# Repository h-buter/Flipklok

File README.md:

# Flipklok in 1970s Style with DCF77 Time Synchronization

|  |  |
|----------------------------|-----------------------------|
|                        |                        |

Welcome to the repository for my project as part of my Bachelor's degree in Electronics at Windesheim. This
project involves creating a flip clock inspired by the design from the 1970s, which is synchronized using time
information from the DCF77 long-wave time signal. The goal is to ensure that this electronic and electromechanical
device operates efficiently within a low power environment.

At time of writing I am still deciding on if the clock will be used a desk clock or if I build it in to my 1977 Relaint Robin MK1
This is why some design decisions, like low power, are not always directly clear in the scope of a normal clock project.

For the complete documentation see the doxygen documentation hosted on GitHub pages:
- Index: https://h-buter.github.io/Flipklok/index.html
- Start of code: https://h-buter.github.io/Flipklok/main_8c.html 
- Interactive Bill of materials: https://h-buter.github.io/Flipklok/md_extra-docs_2bom.html

## Project Overview

This flip clock project integrates both mechanical components and electronics to display the current time
accurately based on data received from the DCF77 transmitter located in Germany. Designed with energy efficiency
in mind, the clock maintains continuous time tracking to compensate for any potential reception limitations of the
DCF77 signal while minimizing power consumption.

## Key Challenges

- **Mechanical and Time Management**: The project requires careful application of mechanics and efficient time
management techniques to ensure the device functions optimally on a 12V source.

- **Integration of Electronics and Electromechanics**: Incorporating electronic components like motors and sensors
for position detection into the mechanical design poses significant challenges.

- **PCB Design**: The creation of a custom PCB is necessary to accommodate all electronic components while
maintaining compactness and efficiency.

- **DCF77 Protocol Implementation**: Applying the DCF77 protocol ensures accurate time synchronization. This
involves handling signals and data correctly within the system’s constraints.

- **Software Development**: The software component, developed in C with some sections written in assembly
language, is responsible for processing DCF77 data and controlling stepper or servo motors to operate the flip
clock.

## Project Boundaries

### Software
The software aspect focuses on:
- Processing DCF77 signal data.
- Controlling a stepper/servo motor mechanism to display time changes accurately.

### Hardware
The hardware component involves:
- Integrating electronic and electromechanical components for seamless operation of the flip clock module.
- Receiving and processing DCF77 timing information effectively.

## Getting Started

To get started with this project, you need to:

- Code: 
    - If you want to view the code use the doxygen documentation (see intoduction) or view the source files on GitHub.
    - If you want to run the code, install TI code composer studio and clone this repository.
        - This repo should contain every file to be able to compile the code for the MSP430G2553
- PCB:
    - View the PCB files use the exported pdf: [exported pdf's](https://github.com/h-buter/Flipklok/tree/main/PCB/Flipklok/export)
    - Edit the PCB files, Kicad and clone the repo.
    - Run a production:
        - Download the gerber ZIP and give this to you're favorite PCB manufacturer, it may be possible the etch the board you're self but be warned this is not easy because of the multilayer construction.
        - Order the bom
        - Wait for everything to arrive 
        - Assemble
        - Test, don't let the make smoke out (not optional)
            - First power up test
            - Flash the code, i used a launchpad devboard see page 8 till 10 [link to datasheet of launchpad](https://www.ti.com/lit/ug/slau772a/slau772a.pdf?ts=1743585388312&ref_url=https%253A%252F%252Fwww.ti.com%252Ftool%252FMSP-EXP430G2ET%253FkeyMatch%253Dmsp-exp430g2et%2526tisearch%253Duniversal_search)
- Mechanics:
    - To view the 3d files you can use the free viewing program [Edrawings](https://www.edrawingsviewer.com/download-edrawings)
    - To edit the files you will need Solidworks

## Contribution

Contributions are welcome! Whether it's optimizing the code for better performance or suggesting improvements in
hardware integration, your input is valuable.

## License

This project is licensed under to be determined 

---

Thank you for exploring this unique blend of vintage design and electronics. Should you have any questions
or suggestions regarding this project, feel free to open an issue or contact me directly.

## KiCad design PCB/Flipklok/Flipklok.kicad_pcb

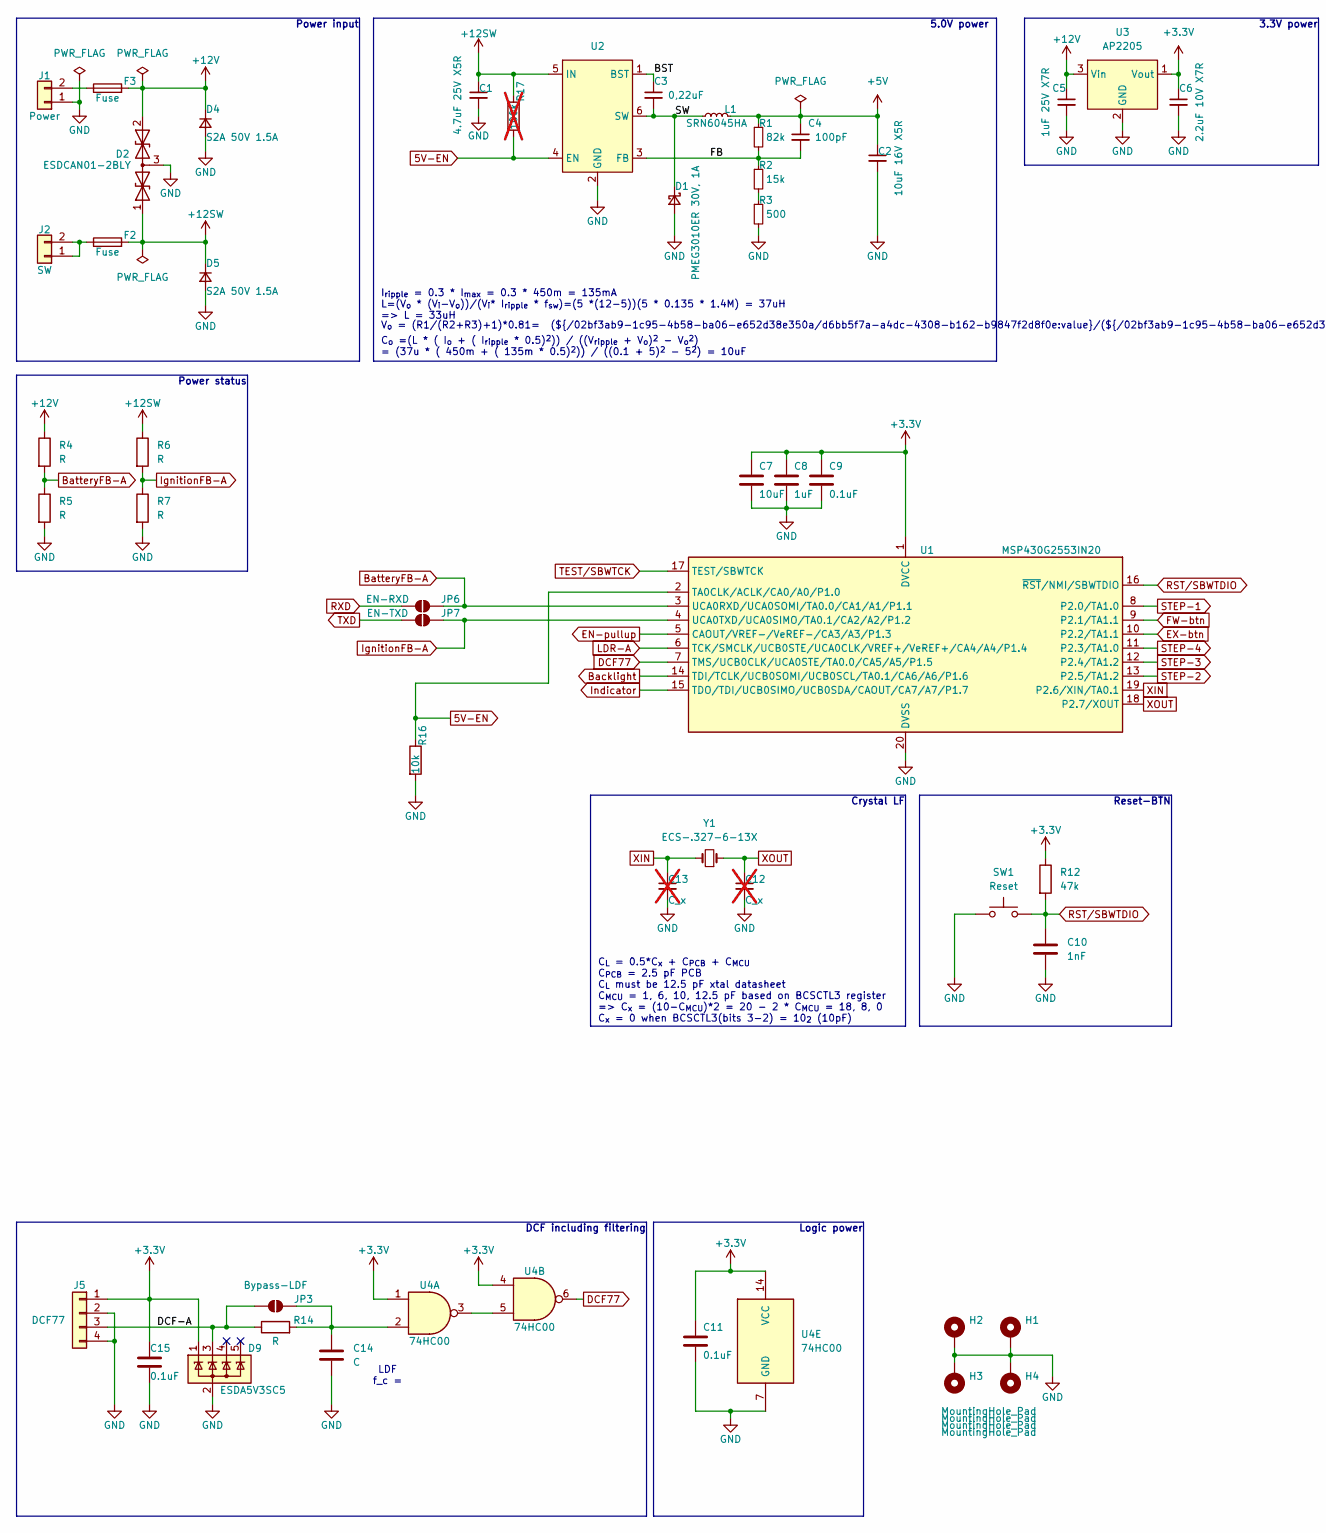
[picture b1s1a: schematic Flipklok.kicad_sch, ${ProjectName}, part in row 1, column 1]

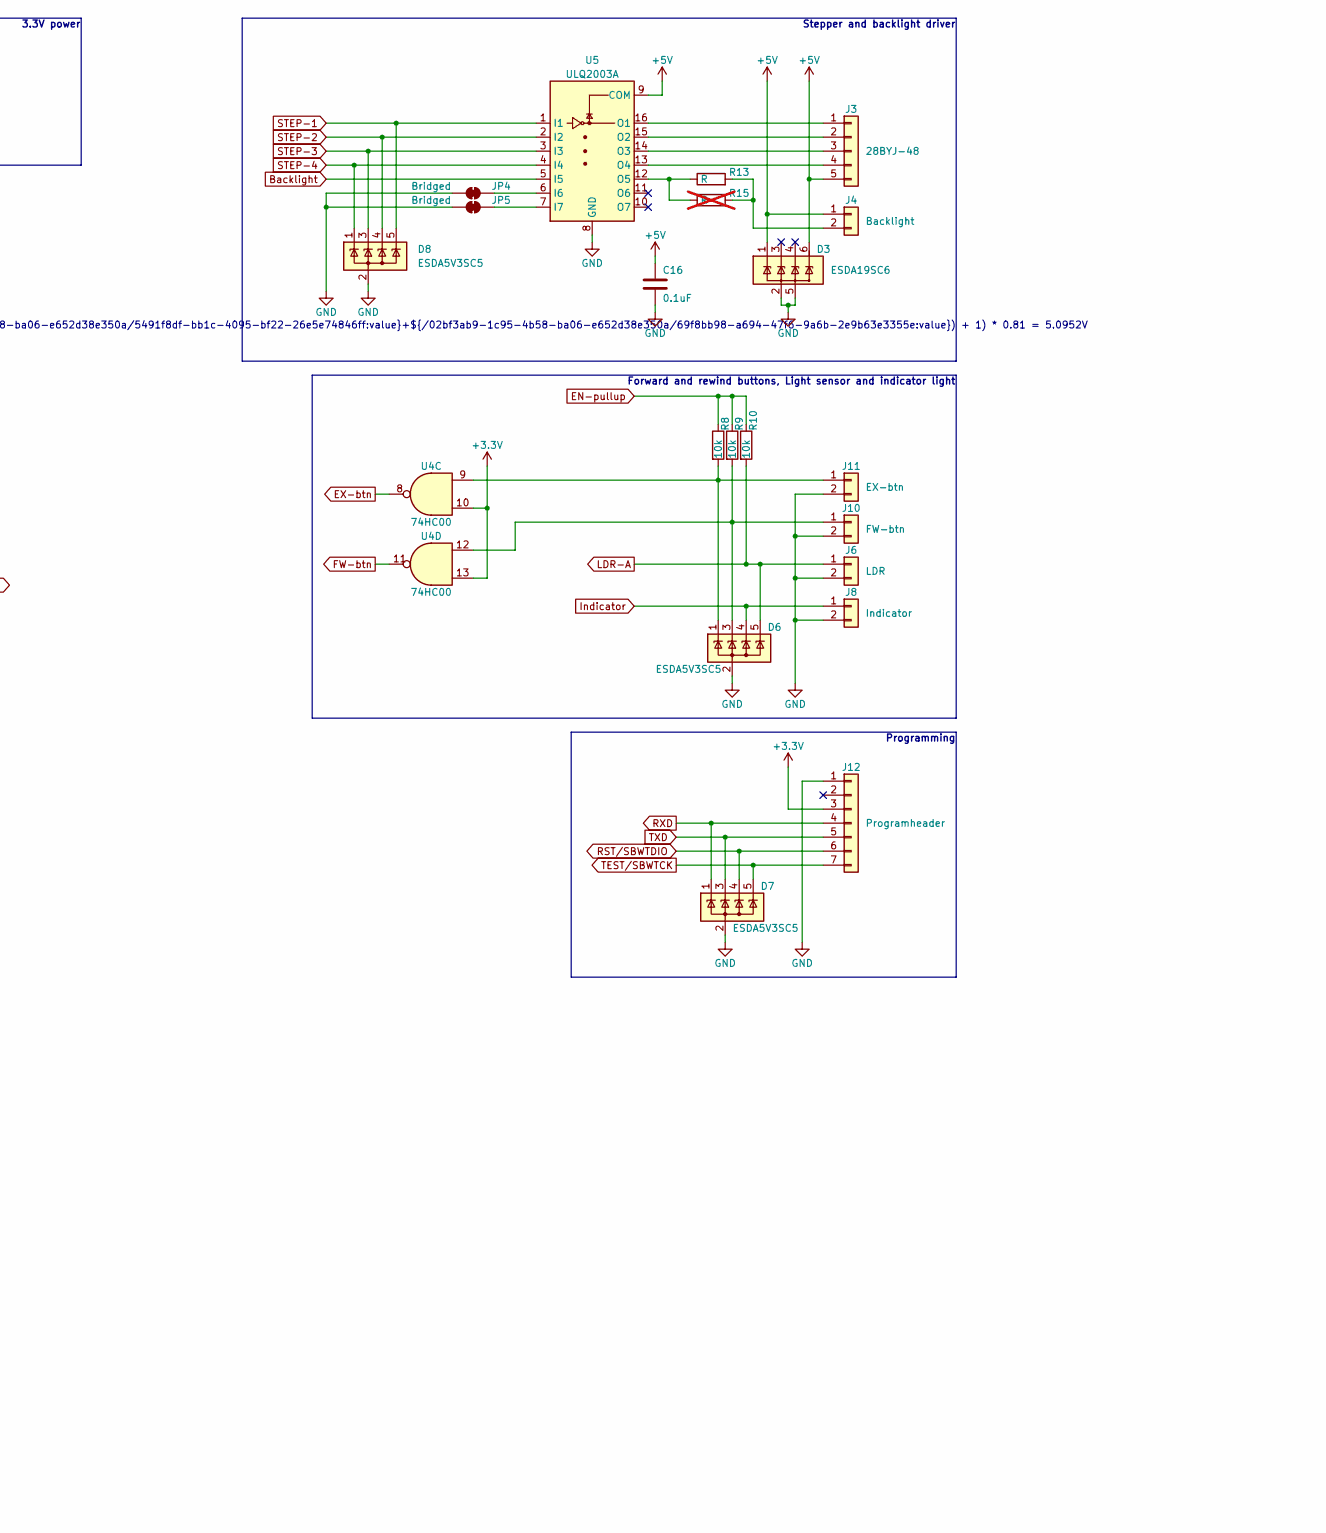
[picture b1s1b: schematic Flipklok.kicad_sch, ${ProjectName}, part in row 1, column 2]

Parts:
C1: 4.7uF 25V X5R; C_0805_2012Metric_Pad1.18x1.45mm_HandSolder
C2: 10uF 16V X5R; C_0805_2012Metric_Pad1.18x1.45mm_HandSolder
C3: 0,22uF; C_0805_2012Metric_Pad1.18x1.45mm_HandSolder
C4: 100pF; C_0805_2012Metric_Pad1.18x1.45mm_HandSolder
C5: 1uF 25V X7R; C_0805_2012Metric_Pad1.18x1.45mm_HandSolder
C6: 2.2uF 10V X7R; C_0805_2012Metric_Pad1.18x1.45mm_HandSolder
C7: 10uF; C_0805_2012Metric_Pad1.18x1.45mm_HandSolder
C8: 1uF; C_0805_2012Metric_Pad1.18x1.45mm_HandSolder
C9, C11, C15, C16: 0.1uF; C_0805_2012Metric_Pad1.18x1.45mm_HandSolder
C10: 1nF; C_0805_2012Metric_Pad1.18x1.45mm_HandSolder
C12, C13: C_x; C_0805_2012Metric_Pad1.18x1.45mm_HandSolder; not fitted
C14: C; C_0805_2012Metric_Pad1.18x1.45mm_HandSolder
D1: PMEG3010ER 30V, 1A; D_SOD-123F
D2: ESDCAN01-2BLY; TSOT-23
D3: ESDA19SC6; SOT-23-6_Handsoldering
D4, D5: S2A 50V 1.5A; D_SMB_Handsoldering
D6, D7, D8, D9: ESDA5V3SC5; SOT-23-5
F2, F3: Fuse; Fuse_0603_1608Metric_Pad1.05x0.95mm_HandSolder
H1, H2, H3, H4: MountingHole_Pad; MountingHole_3.2mm_M3_DIN965_Pad_TopBottom
J1: Power; JST_XH_B2B-XH-A_1x02_P2.50mm_Vertical
J2: SW; JST_XH_B2B-XH-A_1x02_P2.50mm_Vertical
J3: 28BYJ-48; JST_XH_B5B-XH-A_1x05_P2.50mm_Vertical
J4: Backlight; JST_XH_B2B-XH-A_1x02_P2.50mm_Vertical
J5: DCF77; JST_XH_B4B-XH-A_1x04_P2.50mm_Vertical
J6: LDR; JST_XH_B2B-XH-A_1x02_P2.50mm_Vertical
J8: Indicator; JST_XH_B2B-XH-A_1x02_P2.50mm_Vertical
J10: FW-btn; JST_XH_B2B-XH-A_1x02_P2.50mm_Vertical
J11: EX-btn; JST_XH_B2B-XH-A_1x02_P2.50mm_Vertical
J12: Programheader; JST_XH_B7B-XH-A_1x07_P2.50mm_Vertical
JP3: Bypass-LDF; SolderJumper-2_P1.3mm_Open_Pad1.0x1.5mm
JP4, JP5: Bridged; SolderJumper-2_P1.3mm_Bridged_Pad1.0x1.5mm
JP6: EN-RXD; SolderJumper-2_P1.3mm_Open_Pad1.0x1.5mm
JP7: EN-TXD; SolderJumper-2_P1.3mm_Open_Pad1.0x1.5mm
L1: SRN6045HA; L_Bourns_SRN6045TA
R1: 82k; R_0805_2012Metric_Pad1.20x1.40mm_HandSolder
R2: 15k; R_0805_2012Metric_Pad1.20x1.40mm_HandSolder
R3: 500; R_0805_2012Metric_Pad1.20x1.40mm_HandSolder
R4, R5, R6, R7, R13, R14: R; R_0805_2012Metric_Pad1.20x1.40mm_HandSolder
R8, R9, R10, R16: 10k; R_0805_2012Metric_Pad1.20x1.40mm_HandSolder
R12: 47k; R_0805_2012Metric_Pad1.20x1.40mm_HandSolder
R15: R; R_0805_2012Metric_Pad1.20x1.40mm_HandSolder; not fitted
R17: 100k; R_0805_2012Metric_Pad1.20x1.40mm_HandSolder; not fitted
SW1: Reset; SW_Tactile_SPST_NO_Straight_CK_PTS636Sx25SMTRLFS
U1: MSP430G2553IN20; DIP-20_W7.62mm
U2: SOT-23-6_Handsoldering
U3: AP2205; SOT-89-3_Handsoldering
U4: 74HC00; SOIC-14_3.9x8.7mm_P1.27mm
U5: ULQ2003A; DIP-16_W7.62mm_Socket_LongPads
Y1: ECS-.327-6-13X; Crystal_C26-LF_D2.1mm_L6.5mm_Horizontal

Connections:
5V-EN: R16.1, R17.2, U1.2 (TA0CLK/ACLK/CA0/A0/P1.0), U2.4 (EN)
+3.3V: C6.1, C7.1, C8.1, C9.1, C11.1, C15.1, D9.1 (K), J5.1, J12.3, R12.1, U1.1 (DVCC), U3.1 (Vout), U4.1, U4.4, U4.10, U4.13, U4.14 (VCC)
+5V: C2.1, C4.1, C16.1, D3.1 (IO1), D3.6 (IO5), J3.5, J4.1, L1.2, R1.1, U5.9 (COM)
+12SW: C1.1, D2.1 (A1), D5.1 (K), F2.2, R6.1, R17.1, U2.5 (IN)
+12V: C5.1, D2.2 (A2), D4.1 (K), F3.2, R4.1, U3.3 (Vin)
/BST: C3.1, U2.1 (BST)
/DCF-A: D9.3 (K), J5.3, JP3.1 (A), R14.1
/FB: C4.2, R1.2, R2.1, U2.3 (FB)
/SW: C3.2, D1.1 (K), L1.1, U2.6 (SW)
Backlight: U1.14 (TDI/TCLK/UCB0SOMI/UCB0SCL/TA0.1/CA6/A6/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), U5.5 (I5)
BatteryFB-A: JP6.2 (B), R4.2, R5.1, U1.3 (UCA0RXD/UCA0SOMI/TA0.0/CA1/A1/P1.1)
DCF77: U1.7 (TMS/UCB0CLK/UCA0STE/TA0.0/CA5/A5/P1.5), U4.6
EN-pullup: R8.1, R9.1, R10.1, U1.5 (CAOUT/VREF-/VeREF-/CA3/A3/P1.3)
EX-btn: U1.10 (P2.2/TA1.1), U4.8
FW-btn: U1.9 (P2.1/TA1.1), U4.11
GND: C1.2, C2.2, C5.2, C6.2, C7.2, C8.2, C9.2, C10.2, C11.2, C12.2, C13.2, C14.2, C15.2, C16.2, D1.2 (A), D2.3 (common), D3.2 (GND), D3.5 (IO4), D4.2 (A), D5.2 (A), D6.2 (A), D7.2 (A), D8.2 (A), D9.2 (A), H1.1, H2.1, H3.1, H4.1, J1.1, J5.2, J5.4, J6.2, J8.2, J10.2, J11.2, J12.1, JP4.1 (A), JP5.1 (A), R3.2, R5.2, R7.2, R16.2, SW1.1, U1.20 (DVSS), U2.2 (GND), U3.2 (GND), U4.7 (GND), U5.8 (GND)
IgnitionFB-A: JP7.2 (B), R6.2, R7.1, U1.4 (UCA0TXD/UCA0SIMO/TA0.1/CA2/A2/P1.2)
Indicator: D6.4 (K), J8.1, U1.15 (TDO/TDI/UCB0SIMO/UCB0SDA/CAOUT/CA7/A7/P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)
LDR-A: D6.5 (K), J6.1, R10.2, U1.6 (TCK/SMCLK/UCB0STE/UCA0CLK/VREF+/VeREF+/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)
unnamed: F3.1, J1.2
unnamed: F2.1, J2.1, J2.2
unnamed: J3.1, U5.16 (O1)
unnamed: J3.2, U5.15 (O2)
unnamed: J3.3, U5.14 (O3)
unnamed: J3.4, U5.13 (O4)
unnamed: J4.2, R13.2, R15.2
unnamed: D6.3 (K), J10.1, R9.2, U4.12
unnamed: D6.1 (K), J11.1, R8.2, U4.9
unnamed: C14.1, JP3.2 (B), R14.2, U4.2
unnamed: JP4.2 (B), U5.6 (I6)
unnamed: JP5.2 (B), U5.7 (I7)
unnamed: R2.2, R3.1
unnamed: U4.3, U4.5
unnamed: R13.1, R15.1, U5.12 (O5)
RST/SBWTDIO: C10.1, D7.4 (K), J12.6, R12.2, SW1.2, U1.16 (~RST/NMI/SBWTDIO)
RXD: D7.1 (K), J12.4, JP6.1 (A)
STEP-1: D8.5 (K), U1.8 (P2.0/TA1.0), U5.1 (I1)
STEP-2: D8.4 (K), U1.13 (P2.5/TA1.2), U5.2 (I2)
STEP-3: D8.3 (K), U1.12 (P2.4/TA1.2), U5.3 (I3)
STEP-4: D8.1 (K), U1.11 (P2.3/TA1.0), U5.4 (I4)
TEST/SBWTCK: D7.5 (K), J12.7, U1.17 (TEST/SBWTCK)
TXD: D7.3 (K), J12.5, JP7.1 (A)
XIN: C13.1, U1.19 (P2.6/XIN/TA0.1), Y1.2
XOUT: C12.1, U1.18 (P2.7/XOUT), Y1.1

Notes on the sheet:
Power status
I_{ripple} = 0.3 * I_{max} = 0.3 * 450m = 135mA L=(V_{o} * (V_{i}-V_{o}))/(V_{i}* I_{ripple} * f_{sw})=(5 *(12-5))(5 * 0.135 * 1.4M) = 37uH => L = 33uH
LDF f_c =
Power input
Reset-BTN
C_{o} =(L * ( I_{o} + ( I_{ripple} * 0.5)^{2})) / ((V_{ripple} + V_{o})^{2} - V_{o}^{2}) = (37u * ( 450m + ( 135m * 0.5)^{2})) / ((0.1 + 5)^{2} - 5^{2}) = 10uF
5.0V power
Crystal LF
C_{L} = 0.5*C_{x} + C_{PCB} + C_{MCU} C_{PCB} = 2.5 pF PCB C_{L} must be 12.5 pF xtal datasheet C_{MCU} = 1, 6, 10, 12.5 pF based on BCSCTL3 register => C_{x} = (10-C_{MCU})*2 = 20 - 2 * C_{MCU} = 18, 8, 0 C_{x} = 0 when BCSCTL3(bits 3-2) = 10_{2} (10pF)
3.3V power
V_{o} = (R1/(R2+R3)+1)*0.81= (${/02bf3ab9-1c95-4b58-ba06-e652d38e350a/d6bb5f7a-a4dc-4308-b162-b9847f2d8f0e:value}/(${/02bf3ab9-1c95-4b58-ba06-e652d38e350a/5491f8df-bb1c-4095-bf22-26e5e74846ff:value}+${/02bf3ab9-1c95-4b58-ba06-e652d38e350a/69f8bb98-a694-47f6-9a6b-2e9b63e3355e:value}) + 1) * 0.81 = 5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
Forward and rewind buttons, Light sensor and indicator light
DCF including filtering
Programming
Stepper and backlight driver
Logic power

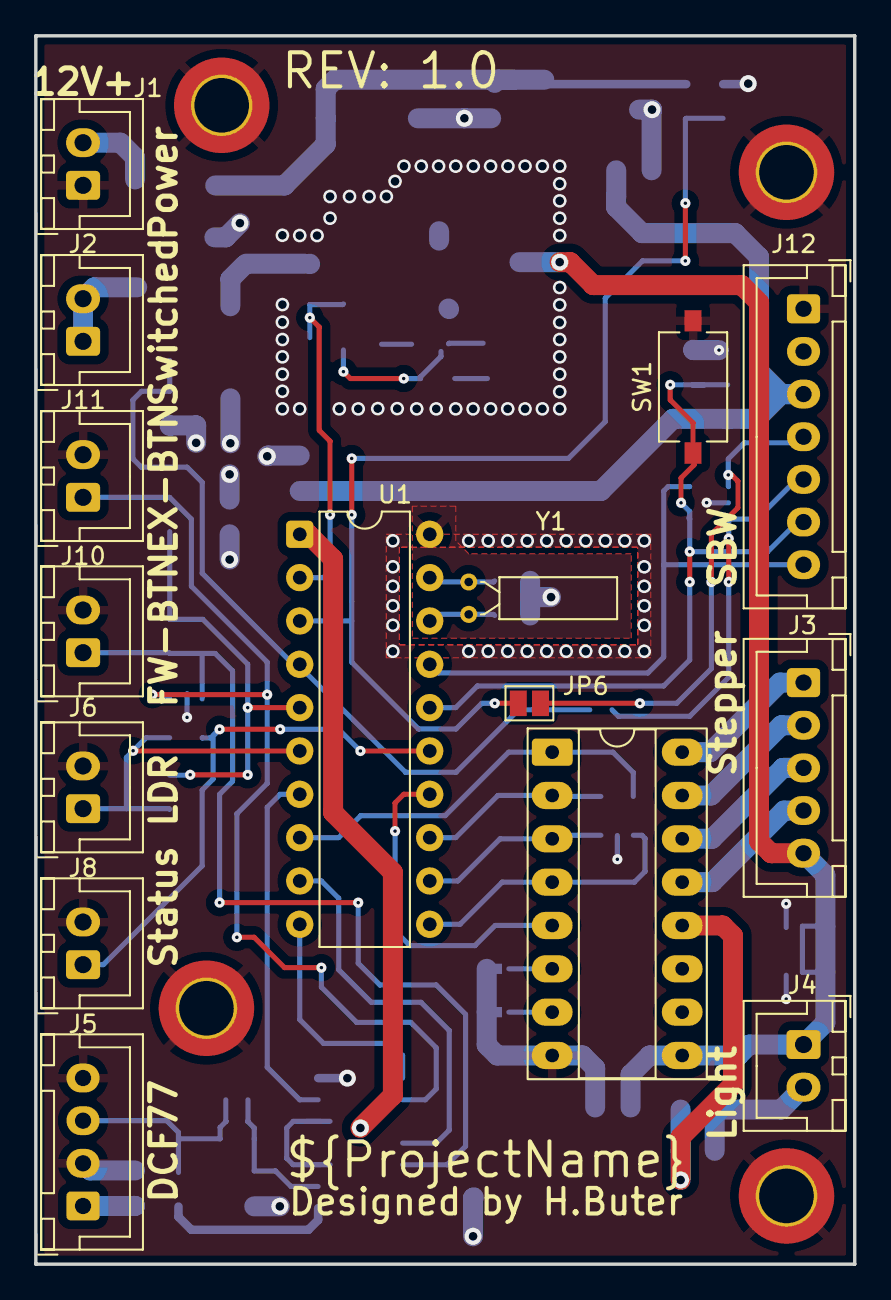
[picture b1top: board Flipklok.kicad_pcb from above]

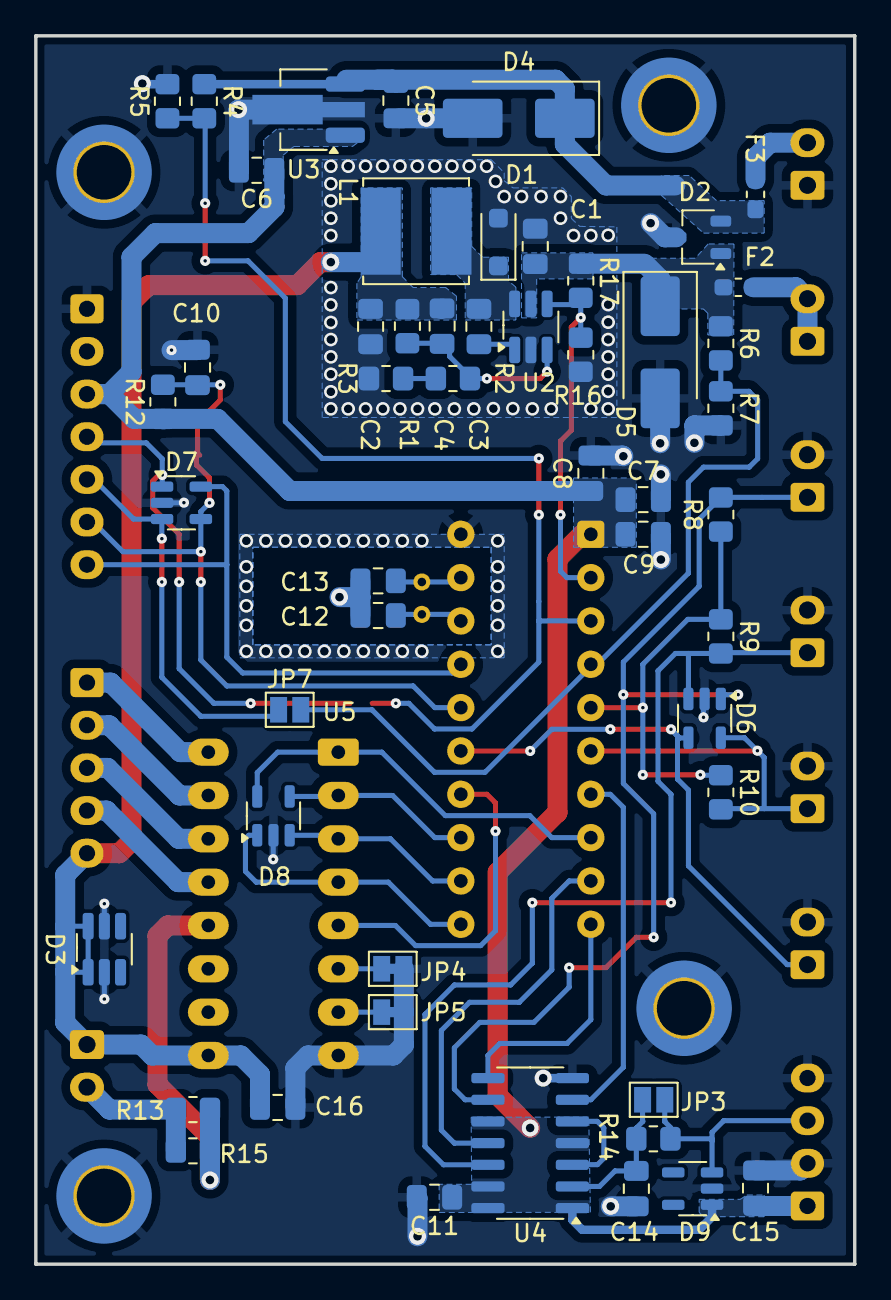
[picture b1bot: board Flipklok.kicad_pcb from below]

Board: 2 copper layers, 48.0 x 72.0 mm, 70 parts (51 on the bottom side), 44 nets.

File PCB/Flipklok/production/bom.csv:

Designator,Footprint,Quantity,Value,LCSC Part #
C1,0805,1,4.7uF 25V X5R,
C10,0805,1,1nF,
"C11, C15, C16, C9",0805,4,0.1uF,
C14,0805,1,C,
C2,0805,1,10uF 16V X5R,
C3,0805,1,"0,22uF",
C4,0805,1,100pF,
C5,0805,1,1uF 25V X7R,
C6,0805,1,2.2uF 10V X7R,
C7,0805,1,10uF,
C8,0805,1,1uF,
D1,D_SOD-123F,1,"PMEG3010ER 30V, 1A",
D2,TSOT-23,1,ESDCAN01-2BLY,
D3,SOT-23-6_Handsoldering,1,ESDA19SC6,
"D4, D5",D_SMB_Handsoldering,2,S2A 50V 1.5A,
"D6, D7, D8, D9",SOT-23-5,4,ESDA5V3SC5,
"F2, F3",0603,2,Fuse,
J1,JST_XH_B2B-XH-A_1x02_P2.50mm_Vertical,1,Power,
J10,JST_XH_B2B-XH-A_1x02_P2.50mm_Vertical,1,FW-btn,
J11,JST_XH_B2B-XH-A_1x02_P2.50mm_Vertical,1,EX-btn,
J12,JST_XH_B7B-XH-A_1x07_P2.50mm_Vertical,1,Programheader,
J2,JST_XH_B2B-XH-A_1x02_P2.50mm_Vertical,1,SW,
J3,JST_XH_B5B-XH-A_1x05_P2.50mm_Vertical,1,28BYJ-48,
J4,JST_XH_B2B-XH-A_1x02_P2.50mm_Vertical,1,Backlight,
J5,JST_XH_B4B-XH-A_1x04_P2.50mm_Vertical,1,DCF77,
J6,JST_XH_B2B-XH-A_1x02_P2.50mm_Vertical,1,LDR,
J8,JST_XH_B2B-XH-A_1x02_P2.50mm_Vertical,1,Indicator,
L1,L_Bourns_SRN6045TA,1,SRN6045HA,
R1,0805,1,82k,
"R10, R16, R8, R9",0805,4,10k,
R12,0805,1,47k,
"R13, R14, R4, R5, R6, R7",0805,6,R,
R2,0805,1,15k,
R3,0805,1,500,
RESET,SW_Tactile_SPST_NO_Straight_CK_PTS636Sx25SMTRLFS,1,Reset,
U1,DIP-20_W7.62mm,1,MSP430G2553IN20,
U2,SOT-23-6_Handsoldering,1,~,
U3,SOT-89-3_Handsoldering,1,AP2205,
U4,SOIC-14_3.9x8.7mm_P1.27mm,1,74HC00,
U5,DIP-16_W7.62mm_Socket_LongPads,1,ULQ2003A,
Y1,Crystal_C26-LF_D2.1mm_L6.5mm_Horizontal,1,ECS-.327-6-13X,

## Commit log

2025-03-03 Update Readme
    added basic project info
2025-03-06 started working on dcf receive test
2025-03-10 Finished basic DCF and NTP check to test DCF77 module reliability
2025-03-10 Started working on mechanics mounting the stepper motor
2025-03-10 Added influxDB support to log errors
2025-03-10 Started working on motor holder v2
2025-03-11 Initial schematic commit Started working on schematic
2025-03-11 Revert "Initial schematic commit Started working on schematic"
    This reverts commit 41658e12fd88ed23b74b87337d35702dc5f5711a.
2025-03-12 Finished REV1.0 of schematic, started working on PCB
2025-03-13 Started optimizing routing and layout
2025-03-14 Finished lay-out and exported gerbers
2025-03-14 Finished drawing the gears and including them in the main assembly
2025-03-17 exported plots of pcb and schematic
2025-03-17 added production backups to gitignore
2025-03-17 deleted zip
2025-03-17 Started design on case
2025-03-18 Finished case
2025-03-18 added step file and needed symbol lib
    Step file contains PCB including 3d components
    Added the custom symbol library for the components: AP2205-33YR-13, AP5100W, ESDA19C6
2025-03-19 Visualized the influxdb data
2025-03-19 include svg in readme file
2025-03-19 Reformat readme
2025-03-19 started code compose studio project
    added code composerstudio specific files to gitignore
2025-03-20 added: doxygen config, started working on steppeAdvance code
2025-03-20 added stepper motor and fwdButton function
2025-03-21 added ADC and led/ldr control
2025-03-21 started working on time keeping
2025-03-21 editted screw and insert dimensions based on testing
2025-03-24 started working on dcf77 simulator
2025-03-24 finished timekeeping started working on DCF77 receive
2025-03-25 generated interactive BOM for assembly
2025-03-25 filled in "to be detriment values" and updated BOM
2025-03-25 filled in led resistor
2025-03-27 Finished rewriting for new devboard and PCB
2025-03-28 Finished DCF emulator
    added epoch test to constantly 'send' out unix epoch time and a function to 'send' the current NTP time
2025-03-28 Finished timing bits and decoding between 1 and 0
    Started working on detecting Sync pulse
2025-03-31 added parity check for dcf77
    Added parity checking of the received dcf77 bits. also checking on bit0, bit20
2025-03-31 fixed timing and added sync bit
    code now implements sync bit between dcf77 messages according to https://wolles-elektronikkiste.de/en/dcf77-radio-controlled-clock
    This help receivers sync with the dcf77 messages, to now when a message starts and ends
2025-04-03 added offset filter and changed to esp32
2025-04-03 commit before rewrite timekeeping
2025-04-03 Time keeping works
    A broken clock is right twice a day, but a working clock is much nicer
2025-04-03 Started working on the documentation
2025-04-04 fixed: adc, fwdButtton, indicatorLed,
    Fixed adc readings
    Fwd button only works when the clock is not syncing
    And the indicator led shows if the clock is on time (off) or off time (on), the brightness is controlled by the LDR
2025-04-07 Revision 2 of backplate
    Moved the PCB more to the side on the backplate to make room for new stepdown converter PCB
2025-04-07 Rewritten timekeeping, added checks, added 5v enable
2025-04-09 Finished working on lowpower settings and rewritten flash
    Flash storage works when debugger is not connected. The debugger overwrites the flash this causes the mechanical time to be not kept across reboots/debug-sessions
2025-04-10 Added documentation
2025-04-10 Documentation doxygen
2025-04-10 moved folder to docs
2025-04-10 moved html folder up
2025-04-10 updated doc added bill of material
2025-04-10 updated doxy, added readme and bom as pages
2025-04-10 Updated the readme
2025-04-10 added pictures
2025-04-10 added picture to markdown doxygen
2025-04-10 fix images in doxygen
2025-04-10 removed export folder
2025-04-10 removed export mechanics
2025-04-10 added the statediagram files
2025-04-10 added state diagram page to doxygen
2025-04-10 Adjusted some pins and disabled epoch time
2025-04-10 fix adc, add uart bitstream, added blinking light when out of sync
2025-04-10 fixed return doxygen
2025-04-10 also for gpio removed return for doxygen
2025-04-10 fixed doxygen param
2025-04-10 fixed param doxygen
2025-04-10 fixed misspelling
2025-04-10 Finished documenting
2025-04-10 Create .gitattributes
    removed html from statistics count on Github
2025-04-10 fixed integer overflow and added button check before setting time on startup
2025-04-15 Updated the docs to include the DCF77 data
